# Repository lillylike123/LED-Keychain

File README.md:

# LED Keychain
My very own mini LED keychain!!! 
It's a cute little LED keychain that changes the animation when moved.
For example, if you pick up your keys, they will have a smiley face!
You can put this on your keys, purse, backpack, or wallet.
I hope you enjoy my first-ever hardware creation.
Made with love <3 by Amira!

No picture yet cause it's not assembled!

| Component | Description | Quantity |
| :--- | :--- | :--- |
| **Microcontroller** | Seeed Studio XIAO ESP32-C3 | 1 |
| **LED Matrix** | WS2812B 8x8 LED Matrix | 1 |
| **Sensor** | PIR Motion Sensor | 1 |
| **Battery** | LiPo Battery (3.7V) | 1 |
| **Connector** | JST-PH 2.0mm 2-pin (Battery) | 1 |
| **Headers** | 2.54mm Pitch Header Pins | ~15 |
| **PCB** | Custom "Bitlace" PCB (34mm x 34mm) | 1 |
| **Fasteners** | M2 x 6mm Machine Screws | 4 |
| **Enclosure** | 3D Printed Case (PLA/PETG) | 1 Set |
| **Misc** | 22AWG Silicone Wire | As needed |

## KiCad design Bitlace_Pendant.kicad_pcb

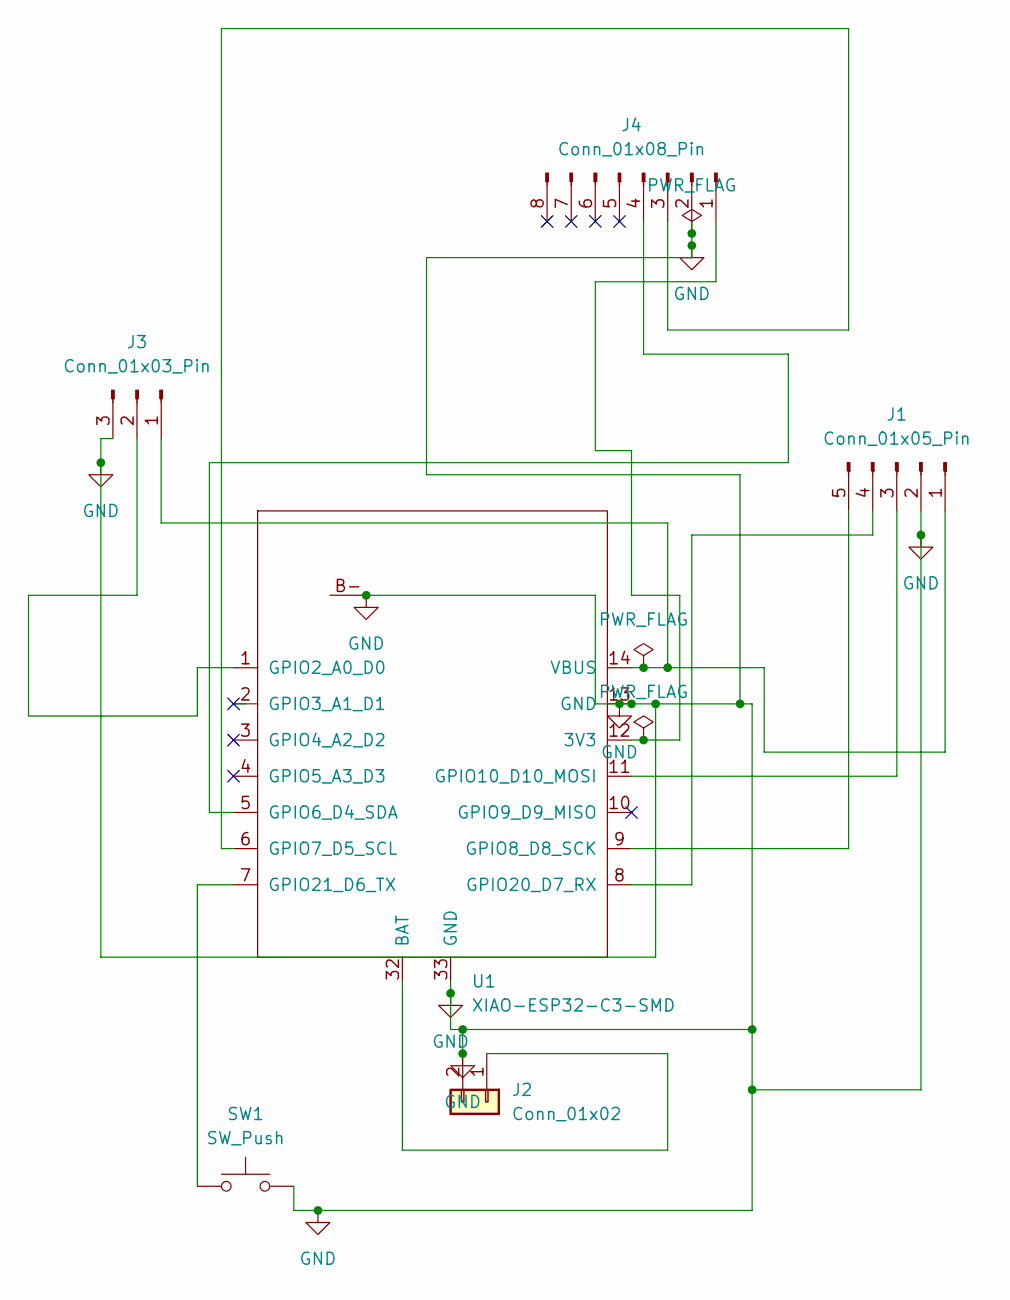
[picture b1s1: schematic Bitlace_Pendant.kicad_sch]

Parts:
J1: Conn_01x05_Pin; PinHeader_1x05_P2.54mm_Vertical
J2: Conn_01x02; JST_PH_S2B-PH-K_1x02_P2.00mm_Horizontal
J3: Conn_01x03_Pin; PinHeader_1x05_P2.54mm_Vertical
J4: Conn_01x08_Pin; PinHeader_1x08_P2.54mm_Vertical
SW1: SW_Push; SW_Tactile_SPST_Angled_PTS645Vx31-2LFS
U1: XIAO-ESP32-C3-SMD; xiao_esp32c3 (1)

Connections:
GND: J1.2, J2.2, J3.3, J4.2, SW1.2, U1.13 (GND), U1.33 (GND), U1.B-
unnamed: J1.1, J3.1, U1.14 (VBUS)
unnamed: J1.3, U1.11 (GPIO10_D10_MOSI)
unnamed: J1.4, U1.8 (GPIO20_D7_RX)
unnamed: J1.5, U1.9 (GPIO8_D8_SCK)
unnamed: J2.1, U1.32 (BAT)
unnamed: J3.2, U1.1 (GPIO2_A0_D0)
unnamed: J4.1, U1.12 (3V3)
unnamed: J4.3, U1.6 (GPIO7_D5_SCL)
unnamed: J4.4, U1.5 (GPIO6_D4_SDA)
unnamed: SW1.1, U1.7 (GPIO21_D6_TX)

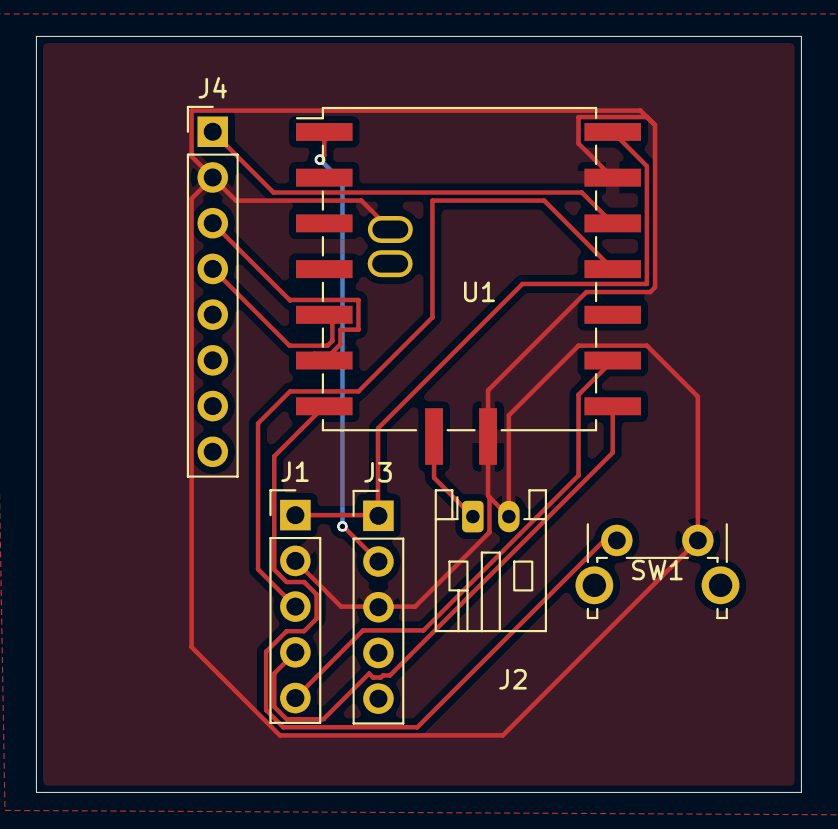
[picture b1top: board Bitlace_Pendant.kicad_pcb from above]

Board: 2 copper layers, 42.5 x 42.0 mm, 6 parts (0 on the bottom side), 11 nets.

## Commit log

2026-06-17 Add journal entry for July 17, 2026
    Documented progress on project schematic and plans for PCB and coding.
2026-06-17 Added html bitlace live companion
2026-06-18 Revise journal entries for project updates
    Updated journal entries with additional details about project progress, including schematic completion, coding tasks, and changes to project design.
2026-06-18 Add new entry for 4:00 hour
2026-06-18 Change project from Bitlace to LED Keychain
    Updated project description to reflect new hardware creation.
2026-06-18 Add motion sensor control for LED modes
2026-06-18 Update journal with PCB and 3D case progress
    Documented the progress on PCB design and 3D case creation for a hardware project, including challenges faced and tools used.
2026-06-18 Update README to mention missing picture
    Added a note about the absence of an image due to assembly status.
2026-06-18 Complete PCB design and 3D case creation
    Finalized PCB design and created a 3D case for the project.
2026-06-18 Document microcontroller and motion sensor coding
    Added details about coding the microcontroller and motion sensors.
2026-06-18 Edit journal
2026-06-18 Add components table to README
    Added a components table with descriptions and quantities.
2026-06-18 Rename code.ino to firmware.ino
2026-06-19 Update journal with new image
